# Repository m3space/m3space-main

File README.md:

# M3 Space Development Repository

This is the main development repository, containing:
* source code for ground control software
* source code for capsule firmware
* source code for live tracker software
* hardware documentation

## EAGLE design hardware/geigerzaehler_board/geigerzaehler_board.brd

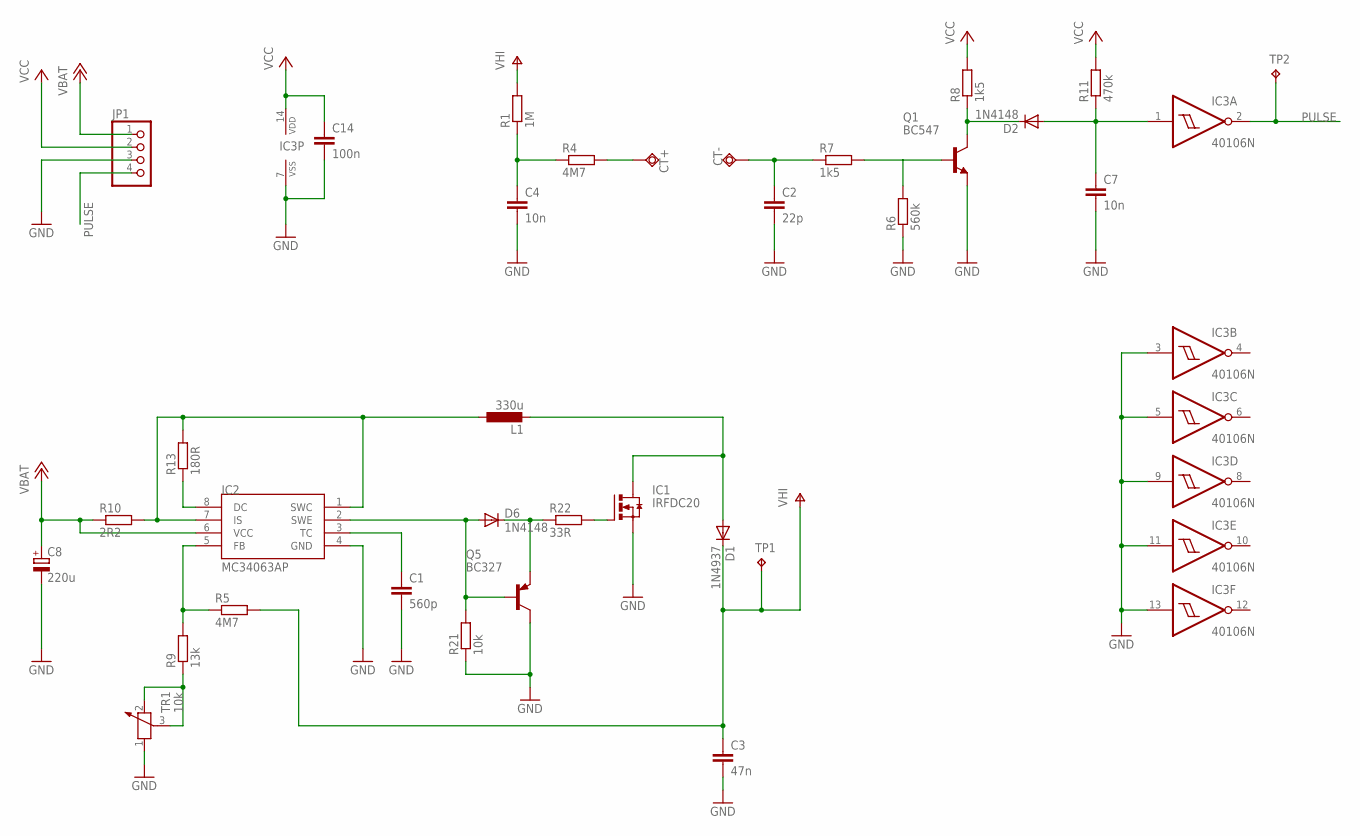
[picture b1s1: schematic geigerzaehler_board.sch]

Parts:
C1: 560p; C025-025X050
C2: 22p; C025-025X050
C3: 47n; C075-052X106
C4: 10n; C075-032X103
C7: 10n; C050-025X075
C8: 220u; E3,5-8
C14: 100n; C050-025X075
CT+: TPSQPAD1-13Y; P1-13Y
CT-: TPSQPAD1-13Y; P1-13Y
D1: 1N4937; DO41-10
D2: 1N4148; DO35-10
D6: 1N4148; DO35-7
IC1: IRFDC20; DIL04
IC2: MC34063AP; DIL08
IC3: 40106N; DIL14
JP1: PINHD-1X4; 1X04
L1: 330u; L-EU5-8
Q1: BC547; TO92
Q5: BC327; TO92
R1: 1M; 0207/10
R4, R5: 4M7; 0207/10
R6: 560k; 0207/10
R7, R8: 1k5; 0207/10
R9: 13k; 0207/10
R10: 2R2; 0309/12
R11: 470k; 0207/10
R13: 180R; 0207/10
R21: 10k; 0207/10
R22: 33R; 0207/10
TP1, TP2: TPPAD1-13Y; P1-13Y
TR1: 10k; PT-SPIN

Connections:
GND: C1.2, C2.2, C3.2, C4.2, C7.2, C8.-, C14.2, IC1.4 (S), IC2.4 (GND), IC3.3 (I), IC3.5 (I), IC3.7 (VSS), IC3.9 (I), IC3.11 (I), IC3.13 (I), JP1.3, Q1.1 (E), Q5.3 (C), R6.1, R21.1, TR1.1
unnamed: D6.A, IC2.2 (SWE), Q5.2 (B), R21.2
unnamed: D6.C, Q5.1 (E), R22.1
unnamed: IC1.3 (G), R22.2
unnamed: D1.A, IC1.1 (D), L1.P$3 (2)
unnamed: IC2.5 (FB), R5.1, R9.2
unnamed: C1.1, IC2.3 (TC)
unnamed: IC2.8 (DC), R13.1
unnamed: IC2.1 (SWC), IC2.7 (IS), L1.P$1 (1), R10.2, R13.2
unnamed: R9.1, TR1.2, TR1.3
unnamed: C4.1, R1.1, R4.1
unnamed: CT+.TP, R4.2
unnamed: C2.1, CT-.TP, R7.1
unnamed: Q1.2 (B), R6.2, R7.2
unnamed: D2.C, Q1.3 (C), R8.1
unnamed: C7.1, D2.A, IC3.1 (I), R11.1
PULSE: IC3.2 (O), JP1.4, TP2.TP
VBAT: C8.+, IC2.6 (VCC), JP1.1, R10.1
VCC: C14.1, IC3.14 (VDD), JP1.2, R8.2, R11.2
VHIGH: C3.1, D1.C, R1.2, R5.2, TP1.TP

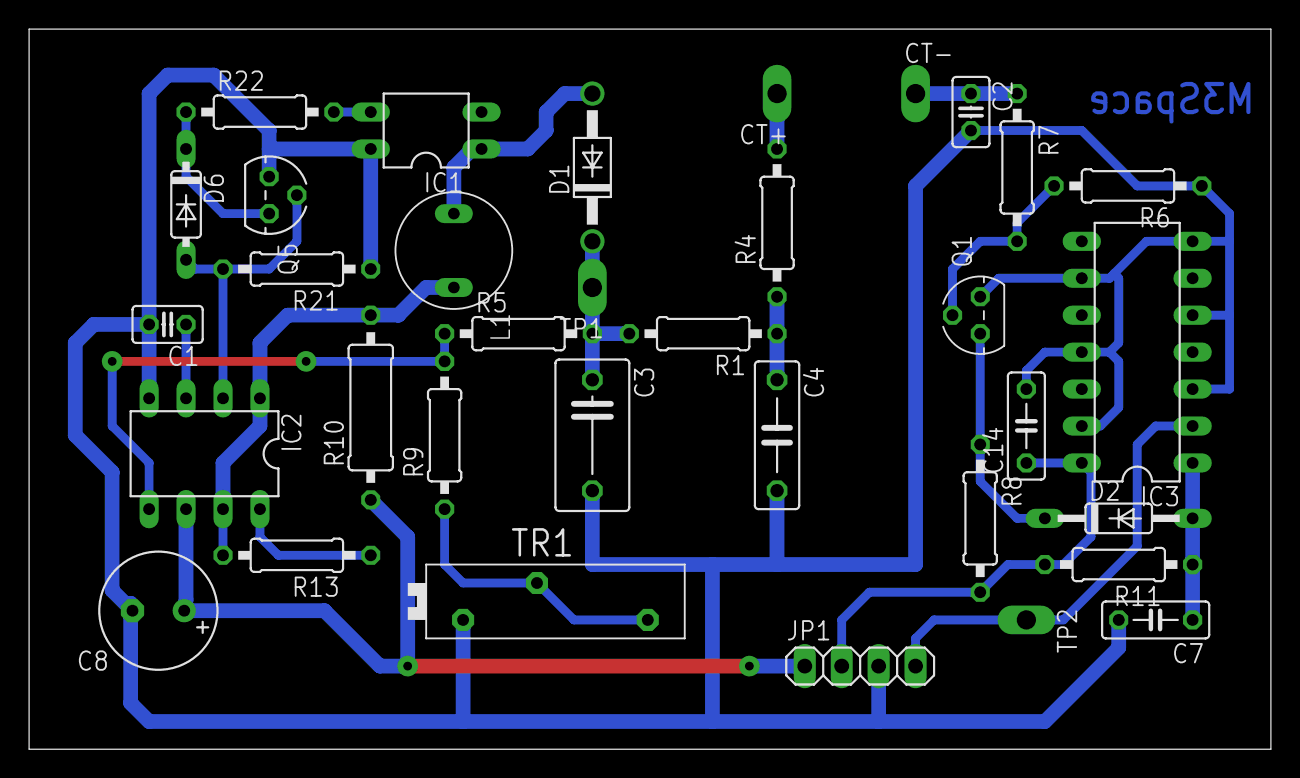
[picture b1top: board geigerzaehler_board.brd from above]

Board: 2 copper layers, 85.4 x 49.5 mm, 34 parts (0 on the bottom side), 20 nets.

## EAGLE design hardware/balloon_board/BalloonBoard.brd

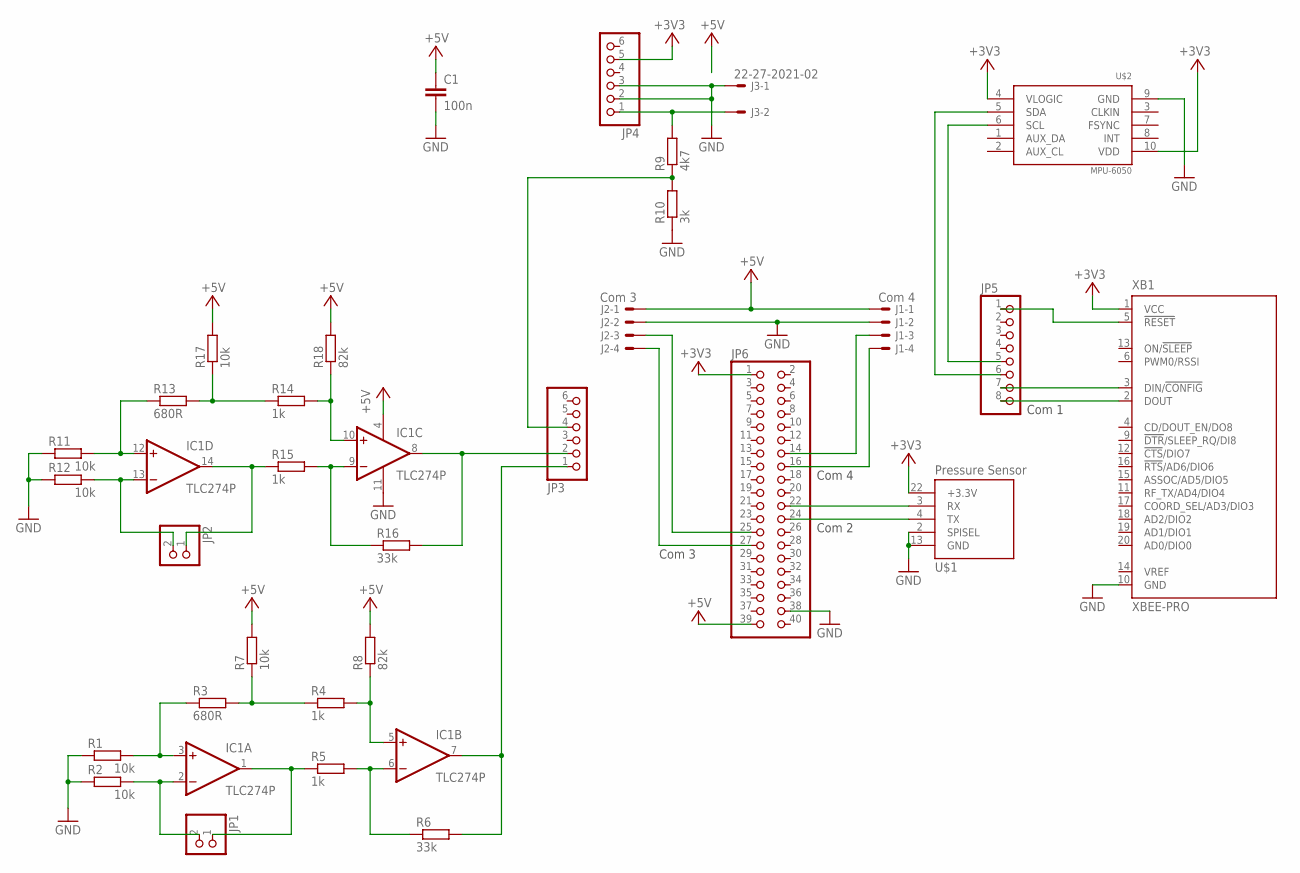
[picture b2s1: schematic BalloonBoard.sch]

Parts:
C1: 100n; C2.5-2
IC1: TLC274P; DIL14
J1: Com 4; 6410-04
J2: Com 3; 6410-04
J3: 22-27-2021-02; 6410-02
JP1, JP2: PINHD-1X2; 1X02
JP3, JP4: PINHD-1X6; 1X06
JP5: PINHD-1X8; 1X08
JP6: PINHD-2X20; 2X20
R1, R2, R7, R11, R12, R17: 10k; 0207/10
R3, R13: 680R; 0207/10
R4, R5, R14: 1k; 0207/10
R6, R16: 33k; 0207/10
R8, R18: 82k; 0207/10
R9: 4k7; 0207/10
R10: 3k; 0207/10
R15: 1k; 0207/12
U$1: PRESSUREMODULE; DIL24
U$2: MPU-6050; MPU-6050_BREAKOUT
XB1: XBEE-PRO

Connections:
+3V3: JP6.1, U$1.22 (+3.3V), XB1.1 (VCC)
+3V3_B: JP4.5, U$2.4 (VLOGIC), U$2.10 (VDD)
+5V: C1.1, IC1.4 (V+), J1.1, J2.1, JP6.39, R7.2, R8.2, R17.2, R18.2
GND: C1.2, IC1.11 (V-), J1.2, J2.2, J3.1, JP4.2, JP4.3, JP6.38, R1.1, R2.1, R10.1, R11.1, R12.1, U$1.2 (SPISEL), U$1.13 (GND), U$2.9 (GND), XB1.10 (GND)
unnamed: IC1.2 (-IN), JP1.2, R2.2
unnamed: IC1.3 (+IN), R1.2, R3.1
unnamed: R3.2, R4.1, R7.1
unnamed: IC1.5 (+IN), R4.2, R8.1
unnamed: IC1.6 (-IN), R5.2, R6.1
unnamed: IC1.1 (OUT), JP1.1, R5.1
unnamed: IC1.13 (-IN), JP2.2, R12.2
unnamed: J3.2, JP4.1, R9.2
unnamed: IC1.7 (OUT), JP3.1, R6.2
unnamed: IC1.12 (+IN), R11.2, R13.1
unnamed: R13.2, R14.1, R17.1
unnamed: IC1.10 (+IN), R14.2, R18.1
unnamed: IC1.9 (-IN), R15.2, R16.1
unnamed: IC1.14 (OUT), JP2.1, R15.1
unnamed: JP5.1, XB1.5 (!RESET)
unnamed: IC1.8 (OUT), JP3.2, R16.2
unnamed: JP5.8, XB1.2 (DOUT)
unnamed: JP5.7, XB1.3 (DIN/!CONFIG)
unnamed: JP3.4, R9.1, R10.2
unnamed: JP5.6, U$2.5 (SDA)
unnamed: J1.3, JP6.14
unnamed: J1.4, JP6.16
unnamed: J2.3, JP6.25
unnamed: J2.4, JP6.27
unnamed: JP5.5, U$2.6 (SCL)
unnamed: JP6.22, U$1.3 (RX)
unnamed: JP6.24, U$1.4 (TX)

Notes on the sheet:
Com 3
Com 4
Com 1
Com 2

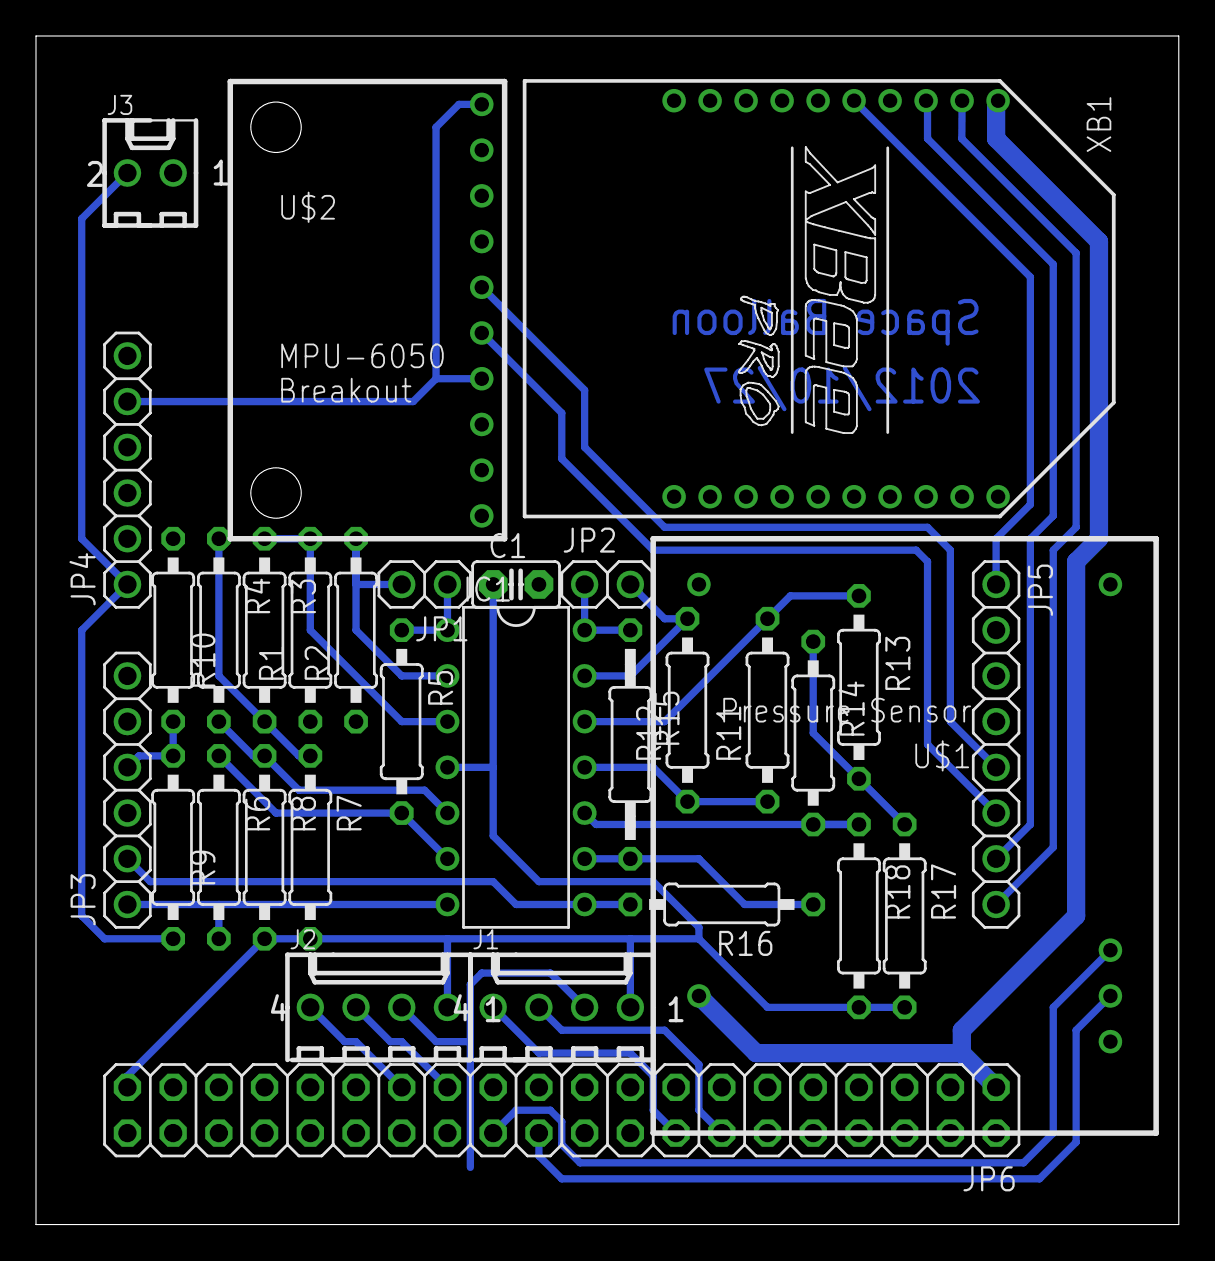
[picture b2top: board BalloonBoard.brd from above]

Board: 2 copper layers, 63.5 x 66.0 mm, 32 parts (0 on the bottom side), 31 nets.

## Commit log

2012-09-26 totally new structure (again)
2012-10-09 added documentation for V3 hardware components
2012-10-09 - data protcol escapes complete packets, no internal buffer used - binary packet converter creates only raw packets without sync bytes - optimized xbee data transmission - image chunk size reduced to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
2012-10-09 improved transmission of live images: - image size is sent with BeginImage - offset is sent with each chunk
2012-10-27 moved hardware drivers into new namespace. added driver for barometer module.
2012-10-27 - removed analog pressure sensor, set values to 0 until barometer is implemented - added vertical speed
2012-10-29 new layout with gyro and pressure sensor
2012-11-04 - added NMEA Parser - connection to GPS - new mapoverlay shows position of groundcontrol - selectable map overlays - added marker icons
2012-11-06 added MPU6050 link
2012-11-11 implemented MPU6050 driver with I2C library
2012-11-12 BallonFirmware: - implemented thread for mpu6050 - implemented thread for barometer
    GroundControl:
    - catch serial port exception of local GPS
    - new data loader for V2 and V3 data
    - added data cache lock to prevent continuing capture on old data files
2012-11-13 - modified barometer code - added new int. temperature from barometer - renamed analog temperatures to temperature 1 and 2
2012-11-13 - removed redundant code - moved formatting strings to DataFormat
2012-11-14 fixed motionthread set barometer serial port delay to 100 ms
2012-11-14 exception handling parsing barometer values
2012-11-15 - set gyro scale to maximum (16g, 2000d/sec) - set heading format to degrees - modified web upload and live web application
2012-11-15 - fixed pressure decoding (mbar -> bar) - fixed web telemetry upload
2012-11-16 optimized I2C bit overwrite
2012-11-16 fixed missing byte cast in I2CSlave
2012-11-16 - added offset to GMapMarkerImage - resized marker icons - implemented burst detection - new colors for routes - displays appropriate balloon icons, hopefully - DataLoader computes vertical speed for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
    - implemented barometer altitude calibration using GPS
2012-11-18 corrected position of the dutycycle byte
2012-11-18 updated graphwindow to new telemetry dataset
2012-11-18 added routeplanner
2012-11-22 started work on new LinkspriteCamera implementation
2012-11-25 - Onboard LED driver - SD-card check - open all filehandles only once - checking all threads periodically and restart if not running - removed altitude adjustment - new offset and gain value for each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
2012-12-30 implemented new GPS driver
2013-01-02 implemented new camera driver
2013-01-03 implemented new camera driver in SpaceBalloon
2013-03-24 added app Balloon AR. this app will track an object by using GPS, android sensors and the camera as augmented reality display.
2013-04-27 updated GMap.net Library
2013-04-27 added VideoPostProcess
2013-04-27 added Aforge dlls
2013-04-27 fixed some minor bugs in VideoPostProcess
2013-05-14 renamed NMEAStandartSentence.cs
2013-05-17 created new project CapsuleFirmware. - integrated new drivers
    - added csv with gyro offset values
2013-05-18 added configuration profile for XBee modules
2013-05-19 - improved camera thread
    - issues: vin is not read, duty cycle is not read
2013-05-27 updated xbee
2013-05-28 - updated XBee profiles - added XBee driver (detached from M3SpaceCapsule) - updated LinkspriteCamera driver
2013-05-29 fixed crash in GroundControl when transceiver is stopped. uses serial port read timeout.
    copied drivers from test branch.
2013-05-30 - updated drivers - Xbee reset after critical duty cycle > 85% - shorter image chunk transmission interval -> slower duty cycle increase - use stop command after taking picture, fixes same picture ta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
2013-05-30 - updated camera driver - telemetry timestamp shows milliseconds -> better motion data accuracy - store live images in sub-directory -> hopefully fixes image capture stopping after 168 images / 3 hou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
2013-05-31 - updated Xbee capsule profile -> no broadcast, ground module is fixed destination - improved vertical speed computation - improved live image decoder
2013-06-01 - altitude and heading are float -> better precision for vertical speed - modified some debug information with VERBOSE flag - changed telemetry window - rearranged code in image transmission thread, 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
2013-06-02 moved vertical speed computation to GpsReader.
    V3 Release Candidate
2013-06-04 added production config.inc.php
2013-06-06 added Predictor
2013-06-12 fixed altitude bug in predictor window predictor launch time is local time
2013-06-18 New project tree structure: - Capsule -> capsule-related software and firmware - GroundControl -> Ground Control until V3 and video processing
2013-06-18 - updated capsule firmware: added conditional compilation (with/without live images) - added new solution for Ground Control 2.0
2013-06-19 GroundControl.Core 2: - added new parameter types - added data container - added test project
2013-06-19 GroundControl.Core.Tests: moved tests
2013-06-21 added motion analysis
2013-06-22 added CapsuleSimulator added parser for Capsule telemetry file
2013-06-22 - implemented motion data processing - added MotionDataConverter -> imports raw motion data, outputs interpolated data
2013-07-26 updated MPU6050. -> capsule firmware fixed, scale is now 16g and 2000deg/s
    fixed CapsuleSimulator (crash when no serial port open)
2013-07-27 fixed live prediction
2013-07-27 - fixed initial predictor map position - allow loading prediction while capturing data
2013-08-05 - display GPS connection state - save visibility of all windows
2013-08-05 prevents using timestamp in the past when running prediction. always adds 1 minute to make sure timestamp is not in the past.
2013-10-15 - improved serial protocol encoding format - fixed loading capsule telemetry in DataLoader - fixed number conversion in DataProtocol packet encoding/decoding
2014-03-27 fixed date format error in DataLoader. fixed .NET micro year offset when using capsule simulator. small optimization of PredictorWindow. added timeout to WebAccess. fixed method not allowed error in 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
2014-03-28 added blog feature
2014-03-28 fixed blog feature
2014-03-29 added utc to blog message
2014-03-29 Prediction from balloon position: added a minute to the timestamp to prevent a datetime in the past
2014-04-23 added Flightradar24
2014-04-23 - added Telemetry Analyzer project - VideoPostprocess: switched Temp1 and Temp2; fixed Gropro3 Video import - GroundControl Core: added V1 telemetry support
2014-04-23 neue XBee-Dokumentation
2014-07-15 added implementation for gamma radiation measurements.
2014-07-27 initial checkin: geigerzähler-board
2014-07-27 completed first version of geigerzähler-board
2014-07-27 optimized geigerzähler-board
2014-08-23 lifted SharpKml to 2.0.1. added tour generator that creates Google Earth tours from telemetry data.
2014-08-28 removed playback speed. not required, because speed can be controlled from Google Earth directly.
2014-08-28 added better balloon burst detection.
2014-08-28 added burst marker for loaded data. fixed burst detection for V2 data.
2014-10-02 better selection of map providers.
2014-10-02 new web uploader using a background task queue.
2014-10-03 fixed bug in DataProtocol. improved web access with better queue. added some modifications to capsule simulator. changed live tracker update interval.
2015-02-02 conditional build option to omit motion data acquisition (mpu6050).
2015-02-03 fixed project setup. added some debugging and rearranged code.
2015-02-06 fixed mismatch of packet sizes. added build option to disable camera. added gamma count to graph window. modified burst detection.
2015-03-04 added CPM counter to telemetry window. added hack to make flightradar24 work again. ghetto but it works.
2015-03-07 improved FlightRadar24. compute CPM after receiving telemetry packet. save CPM and also upload to web service. some improvements to live tracker, also displays CPM now.
2015-04-09 improved live tracker. displays car if gps position available. added script to clear all data.
2015-04-12 implemented upload of GPS position in GroundControl.
2015-04-13 cpm counter values not older than 1 minute
2015-04-13 fixed cpmcounter
2015-04-24 fixed coordinate upload
2016-09-20 Adaptation for Mission 6: barometer and gamma detector are optional, but did not change telemetry format (values are set to 0). Updated GMap.NET libraries. Fixed OpenStreetMap display, Google satelli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
2016-09-21 small refactoring of data formats and display string.
2016-10-13 add readme.
2016-10-13 added gitignore
2016-10-13 more gitignore
